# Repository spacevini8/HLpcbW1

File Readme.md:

# Lambdassistant

## V1

## V2

This device was designed for week one of Hackclub [Half Life](https://halflife.hackclub.com/) (hence the reference)
This is a motion controlled tamagotchi like device comprised of: 
- Five buttons (three main, reset and boot)
- Rotary encoder (also a button)
- AM2302 environment sensor (temp and humidity)
- MPU6050 motion sensor
- GY-302 BH1750 light sensor
- Buzzer
- OLED screen

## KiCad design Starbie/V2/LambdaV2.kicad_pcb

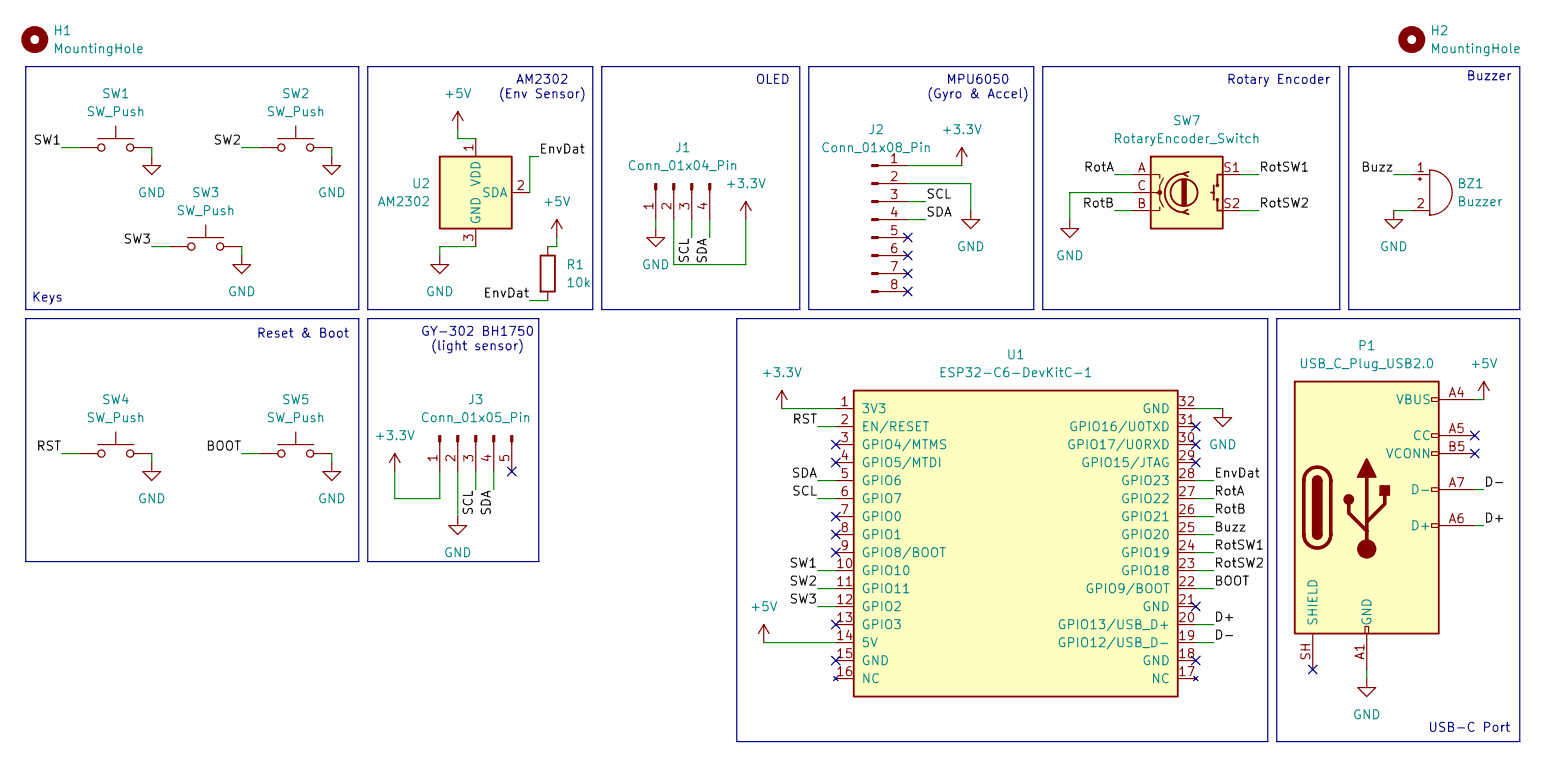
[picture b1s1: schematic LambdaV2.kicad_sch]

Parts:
BZ1: Buzzer; Buzzer_12x9.5RM7.6
H1, H2: MountingHole; MountingHole_5mm
J1: Conn_01x04_Pin; Display_128x64_096_I2C
J2: Conn_01x08_Pin; PinHeader_1x08_P2.54mm_Vertical
J3: Conn_01x05_Pin; PinHeader_1x05_P2.54mm_Vertical
P1: USB_C_Plug_USB2.0; USB_C_Receptacle_G-Switch_GT-USB-7010ASV
R1: 10k; R_Axial_DIN0204_L3.6mm_D1.6mm_P7.62mm_Horizontal
SW1, SW2, SW3: SW_Push; SW_Cherry_MX_1.00u_PCB
SW4, SW5: SW_Push; SW_PUSH_6mm_H5mm
SW7: RotaryEncoder_Switch; RotaryEncoder_Alps_EC11E-Switch_Vertical_H20mm
U1: ESP32-C6-DevKitC-1
U2: AM2302; ASAIR_AM2302_P2.54mm_Vertical

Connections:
+3.3V: J1.2, J2.1, J3.1, U1.1 (3V3)
+5V: P1.A4 (VBUS), P1.A9 (VBUS), P1.B4 (VBUS), P1.B9 (VBUS), R1.1, U1.14 (5V), U2.1 (VDD)
/BOOT: SW5.1, U1.22 (GPIO9/BOOT)
/Buzz: BZ1.1 (+), U1.25 (GPIO20)
/D+: P1.A6 (D+), U1.20 (GPIO13/USB_D+)
/D-: P1.A7 (D-), U1.19 (GPIO12/USB_D-)
/EnvDat: R1.2, U1.28 (GPIO23), U2.2 (SDA)
/RST: SW4.1, U1.2 (EN/RESET)
/RotA: SW7.A, U1.27 (GPIO22)
/RotB: SW7.B, U1.26 (GPIO21)
/RotSW1: SW7.S1, U1.24 (GPIO19)
/RotSW2: SW7.S2, U1.23 (GPIO18)
/SCL: J1.3, J2.3, J3.3, U1.6 (GPIO7)
/SDA: J1.4, J2.4, J3.4, U1.5 (GPIO6)
/SW1: SW1.1, U1.10 (GPIO10)
/SW2: SW2.1, U1.11 (GPIO11)
/SW3: SW3.1, U1.12 (GPIO2)
GND: BZ1.2 (-), J1.1, J2.2, J3.2, P1.A1 (GND), P1.A12 (GND), P1.B1 (GND), P1.B12 (GND), SW1.2, SW2.2, SW3.2, SW4.2, SW5.2, SW7.C, U1.32 (GND), U2.3 (GND), U2.4 (GND)

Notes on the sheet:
USB-C Port
AM2302 (Env Sensor)
Reset & Boot
MPU6050 (Gyro & Accel)
Buzzer
Rotary Encoder
GY-302 BH1750 (light sensor)
Keys
OLED

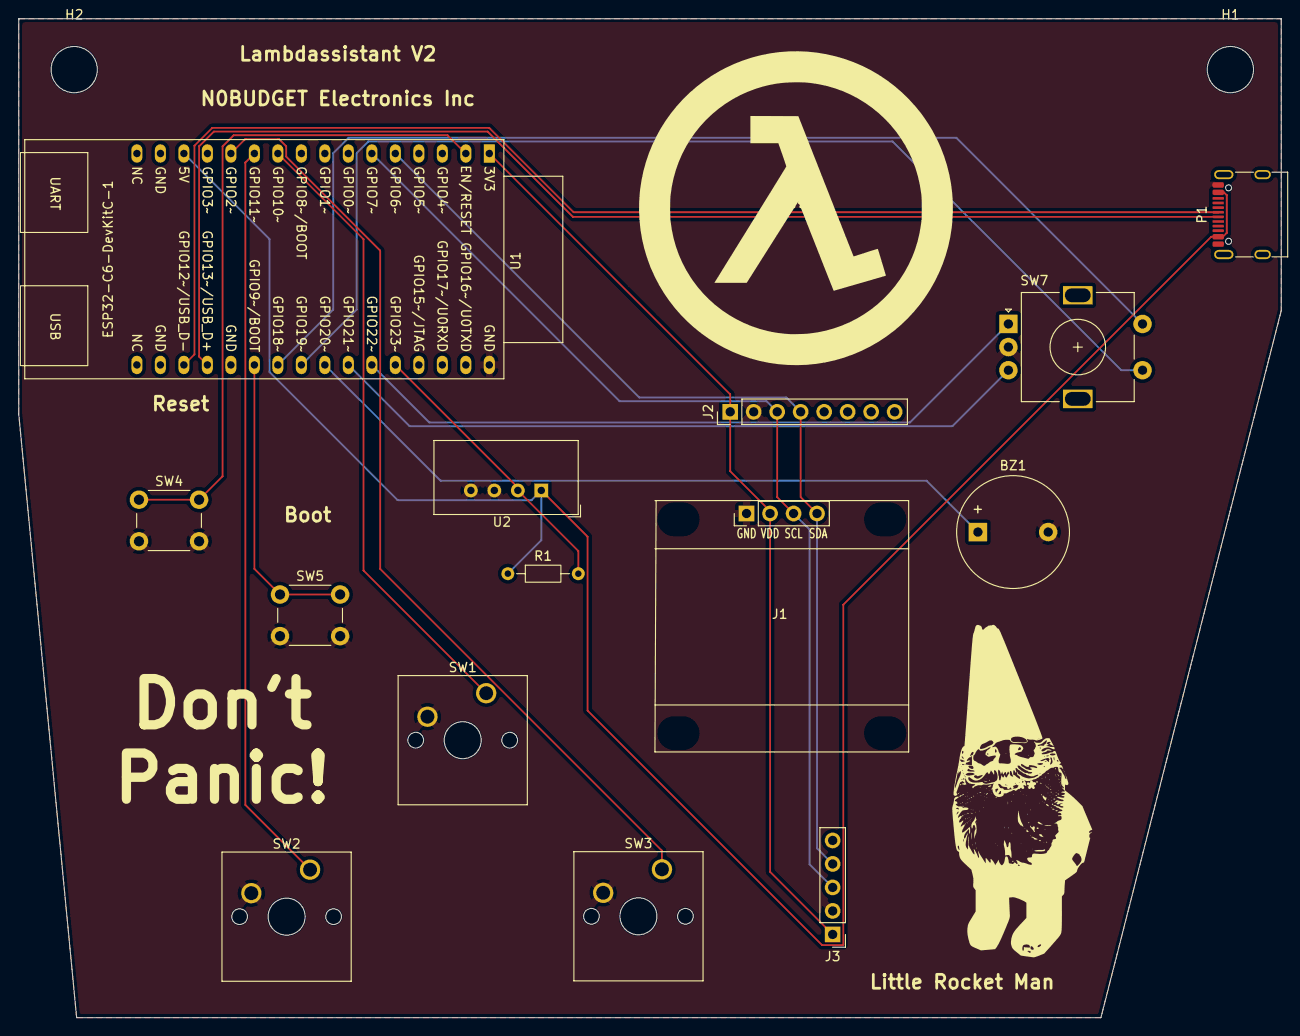
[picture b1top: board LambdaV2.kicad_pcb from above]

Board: 2 copper layers, 136.5 x 108.0 mm, 16 parts (0 on the bottom side), 18 nets.

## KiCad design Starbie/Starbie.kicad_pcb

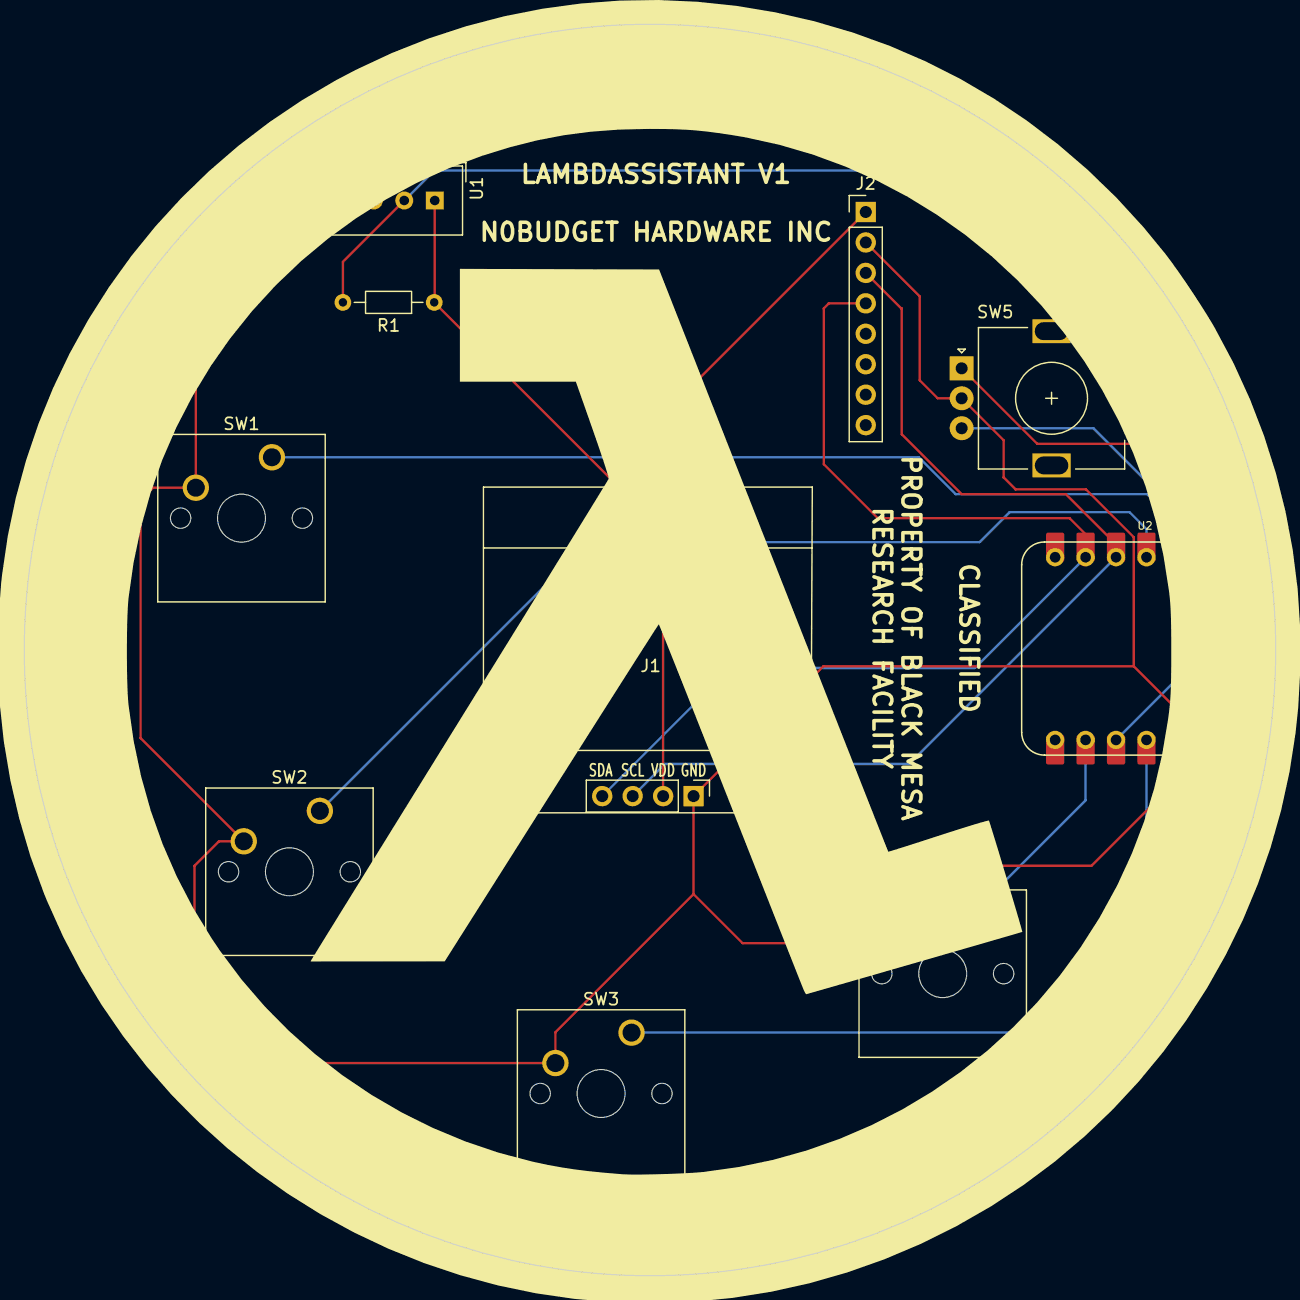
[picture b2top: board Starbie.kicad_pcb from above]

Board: 2 copper layers, 104.4 x 104.4 mm, 11 parts (0 on the bottom side), 11 nets.

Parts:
H1: KeyChainHole; MountingHole_4.5mm
J1: Conn_01x04_Pin; Display_128x64_096_I2C
J2: Conn_01x08_Pin; PinHeader_1x08_P2.54mm_Vertical
R1: 10k; R_Axial_DIN0204_L3.6mm_D1.6mm_P7.62mm_Horizontal
SW1, SW2, SW3, SW4: SW_Push; SW_Cherry_MX_1.00u_PCB
SW5: RotaryEncoder; RotaryEncoder_Alps_EC11E-Switch_Vertical_H20mm
U1: DHT11; Aosong_DHT11_5.5x12.0_P2.54mm
U2: XIAO-ESP32-C3-SMD; XIAO-ESP32-C6-DIP

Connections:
+3.3V: J1.2, J2.1, R1.1, U1.1 (VDD), U2.12 (3V3_OUT)
/DHT11 DATA: R1.2, U1.2 (DATA), U2.2 (D1)
/GPIO2: SW1.1, U2.3 (D2)
/GPIO3: SW2.1, U2.4 (D3)
/GPIO6: SW5.A, U2.1 (D0)
/GPIO7: SW5.B, U2.10 (D9/BOOT)
/GPIO8: SW4.1, U2.9 (D8)
/GPIO10: SW3.1, U2.11 (D10)
/SCL: J1.3, J2.3, U2.5 (D4)
/SDA: J1.4, J2.4, U2.6 (D5)
GND: J1.1, J2.2, SW1.2, SW2.2, SW3.2, SW4.2, SW5.C, U1.4 (GND), U2.13 (GND)

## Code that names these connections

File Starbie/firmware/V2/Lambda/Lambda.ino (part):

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
const int I2C_SDA_PIN = 6;
const int I2C_SCL_PIN = 7;
const int AM2302_PIN = 23; //EnvDat

const int Button_1_PIN = 10; // SW1
const int Button_2_PIN = 11; // SW2
const int Button_3_PIN = 2; // SW3

const int Rotary_A_PIN = 22; // RotA
const int Rotary_B_PIN = 23; // RotB
const int Rotary_SW1_PIN = 19; // RotSW1
const int Rotary_SW2_PIN = 18; // RotSW2

const int Buzzer_PIN = 20; // Buzz

const uint8_t OLED_ADDRESS = 0x3C;
const uint8_t MPU6050_ADDRESS = 0x68;
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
